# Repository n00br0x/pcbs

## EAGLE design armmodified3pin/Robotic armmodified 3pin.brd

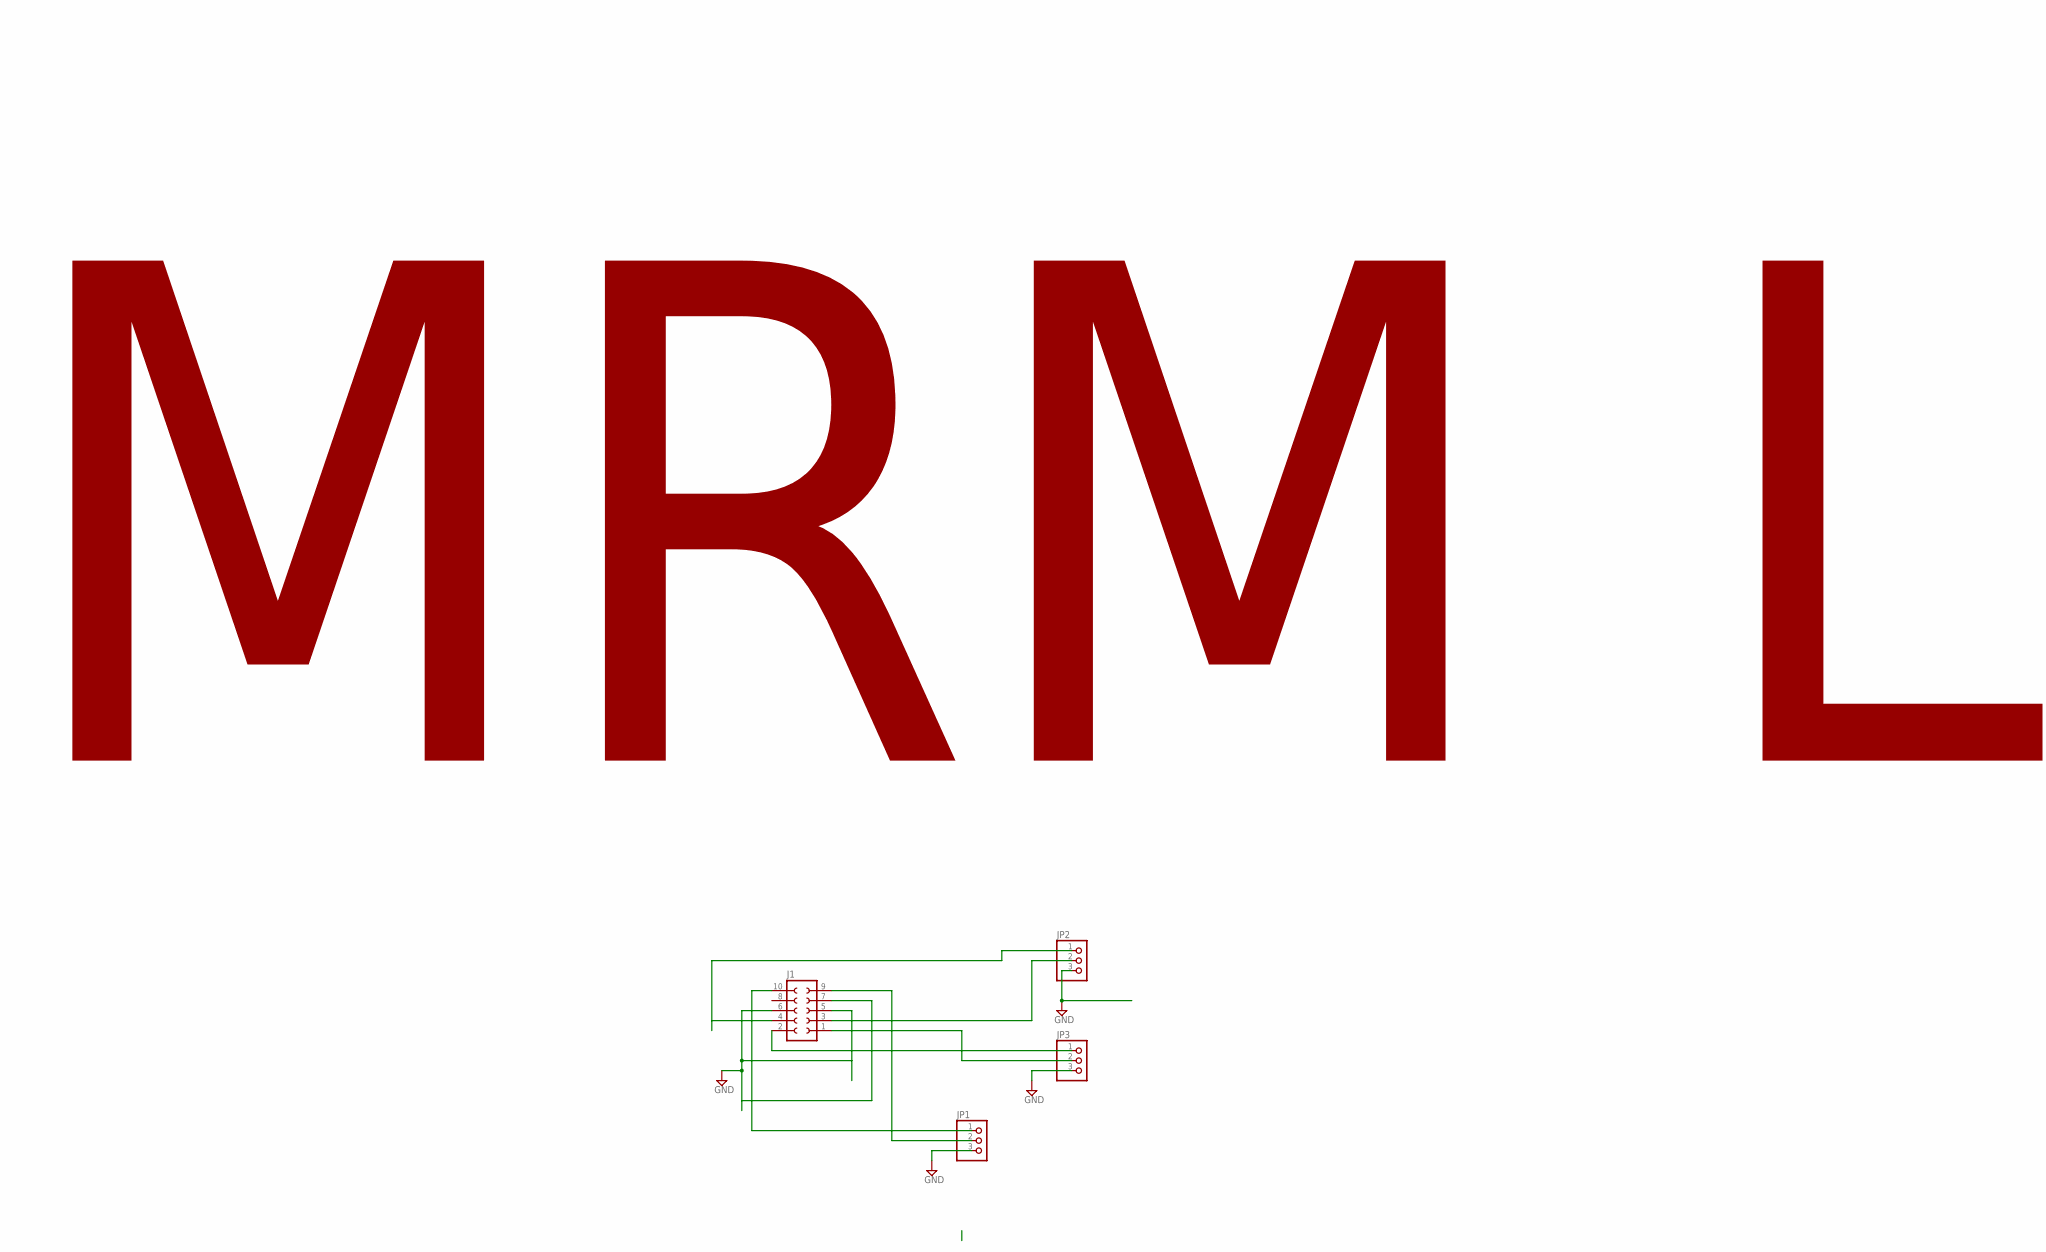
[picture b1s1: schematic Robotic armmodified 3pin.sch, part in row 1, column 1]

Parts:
J1: SOCKET-10V; S10V
JP1, JP2, JP3: PINHD-1X3; 1X03
MRM1: MRM; LOL

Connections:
GND: J1.5, J1.6, J1.7, JP1.3, JP2.3, JP3.3
unnamed: J1.10, JP1.1
unnamed: J1.9, JP1.2
unnamed: J1.1, JP3.2
unnamed: J1.2, JP3.1
unnamed: J1.3, JP2.2
unnamed: J1.4, JP2.1

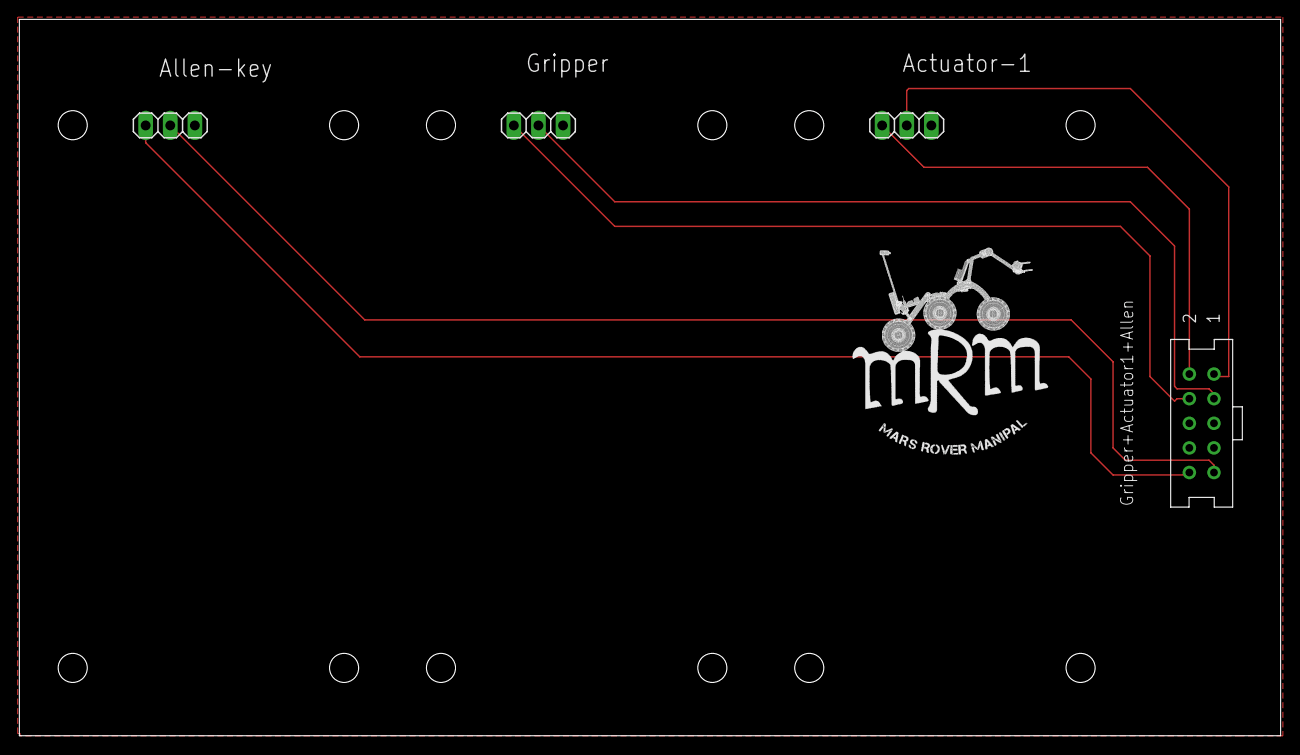
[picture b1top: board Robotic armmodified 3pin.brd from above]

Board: 2 copper layers, 130.1 x 73.9 mm, 5 parts (0 on the bottom side), 7 nets.
